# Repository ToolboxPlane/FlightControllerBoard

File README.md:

View this project on [CADLAB.io](https://cadlab.io/node/744). 

# FlightControllerBoard

A flight controller board for the mini Talon UAV based on a [STM32 Nucleo-32](http://www.st.com/content/st_com/en/products/evaluation-tools/product-evaluation-tools/mcu-eval-tools/stm32-mcu-eval-tools/stm32-mcu-nucleo/nucleo-l432kc.html).

Firmware availiable at [https://github.com/ToolboxBodensee/FlightController](https://github.com/ToolboxBodensee/FlightController).

## PCB

### Top layer

### Bottom Layer

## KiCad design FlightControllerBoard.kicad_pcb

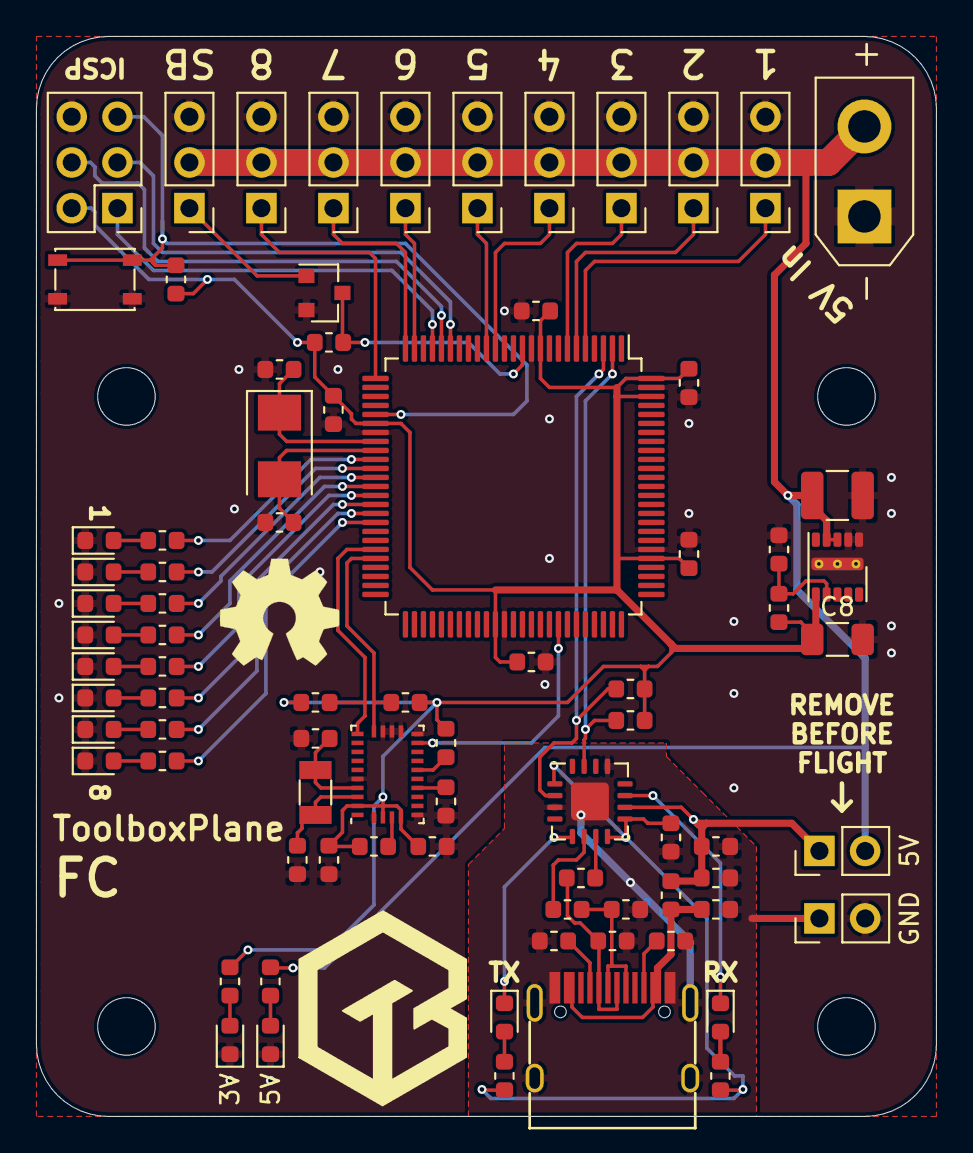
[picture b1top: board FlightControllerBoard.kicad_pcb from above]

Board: 2 copper layers, 50.0 x 60.0 mm, 85 parts (0 on the bottom side), 62 nets.

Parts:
C1, C2: 47p; C_0603_1608Metric
C3: 10nF; C_0603_1608Metric
C4, C6, C11, C12, C13, C14, C15, C16, C17, C18: 100nF; C_0603_1608Metric
C5: 4.7µF; C_0603_1608Metric
C7: 10µF; C_1210_3225Metric
C8: 22µF; C_1206_3216Metric
C9, C10: 8pF; C_0603_1608Metric
C19, C20: 9pF; C_0603_1608Metric
D1, D2: LED; LED_0603_1608Metric
D3, D4: LED_Small; LED_0603_1608Metric
D5, D6, D7, D8, D9, D10, D11, D12: LED_0603_1608Metric
FB1: 600 Ohms @ 100MHz; C_0603_1608Metric
H1, H2, H3, H4: MountingHole; MountingHole_3.2mm_M3
J1: Conn_01x02; AMASS_XT30UPB-M_1x02_P5.0mm_Vertical
J2, J3, J4, J5, J6, J7, J8, J9, J10: Conn_01x03_Male; PinHeader_1x03_P2.54mm_Vertical
J11: USB_C_Receptacle_USB2.0; USB_C_Receptacle_GT-USB-7010
J12: Conn_02x03_Odd_Even; PinHeader_2x03_P2.54mm_Vertical
JP1, JP2: Jumper_NO_Small; PinHeader_1x02_P2.54mm_Vertical
Q1: BSS138; SOT-23
R1, R2, R3: 4.7k; R_0603_1608Metric
R4: 470; R_0603_1608Metric
R5, R10, R11: 270; R_0603_1608Metric
R6, R7: 5.1k; R_0603_1608Metric
R8, R9: 27; R_0603_1608Metric
R12: 11.5k; R_0603_1608Metric
R13: 4.99k; R_0603_1608Metric
R14, R23, R24, R25, R26: 10k; R_0603_1608Metric
R15, R16, R17, R18, R19, R20, R21, R22: 100; R_0603_1608Metric
SW1: SW_Push; SW_SPST_PTS810
U1: FT230XQ; QFN-16-1EP_4x4mm_P0.65mm_EP2.1x2.1mm
U2: LMZM23600; Texas_SIL0010A_MicroSiP-10-1EP_3.8x3mm_P0.6mm_EP0.7x2.9mm_T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
U3: ATmega2560-16AU; TQFP-100_14x14mm_P0.5mm
U4: BNO055; LGA-28_5.2x3.8mm_P0.5mm
Y1: 16MHz; Crystal_SMD_5032-2Pin_5.0x3.2mm
Y2: 32.768kHz; Crystal_SMD_3215-2Pin_3.2x1.5mm

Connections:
+3V3: C8.1, C11.2, C12.2, C13.2, C14.2, C15.2, C16.1, C18.1, J12.2, R1.1, R2.1, R3.1, R5.1, R12.1, R14.1, R23.1, R24.1, R25.1, R26.2, U2.6, U3.10, U3.31, U3.61, U3.80, U3.98, U3.100, U4.3, U4.5, U4.28
+5V: C7.1, J1.2, J2.2, J3.2, J4.2, J5.2, J6.2, J7.2, J8.2, J9.2, J10.2, JP1.2, R4.1, U2.3, U2.4
/ATMega/MISO: J12.1, U3.22
/ATMega/MOSI: J12.4, U3.21
/ATMega/RX0: R1.2, U1.15, U3.2
/ATMega/RX1: R23.2, U3.45, U4.20
/ATMega/SCK: J12.3, U3.20
/ATMega/~RESET~: J12.5, R14.2, SW1.2, U3.30
/BNO/INT: U3.68, U4.14
/BNO/RX: R24.2, U3.46, U4.19
/FT230/5VOUT: C4.1, C5.1, FB1.1, JP1.1, U1.10
/FT230/RX: R2.2, U1.2, U3.3
/PWM1: J2.1, U3.24
/PWM2: J3.1, U3.25
/PWM3: J4.1, U3.26
/PWM4: J5.1, U3.5
/PWM5: J6.1, U3.6
/PWM6: J7.1, U3.7
/PWM7: J8.1, U3.15
/PWM8: J9.1, U3.16
/SBUS: J10.1, Q1.1
/~SBUS: Q1.3, R3.2, U3.12
GND: C7.2, C8.2, C9.2, C10.2, C11.1, C12.1, C13.1, C14.1, C15.1, C16.2, C17.1, C18.2, C19.2, C20.2, D1.1, D2.1, D5.1, D6.1, D7.1, D8.1, D9.1, D10.1, D11.1, D12.1, J1.1, J2.3, J3.3, J4.3, J5.3, J6.3, J7.3, J8.3, J9.3, J10.3, J12.6, JP2.2, Q1.2, R13.1, SW1.1, U2.1, U2.2, U2.11, U3.11, U3.32, U3.62, U3.81, U3.99, U4.2, U4.6, U4.15, U4.16, U4.17, U4.18, U4.25
GNDS: C1.2, C2.2, C3.2, C4.2, C5.2, C6.2, J11.A1, J11.A12, J11.B1, J11.B12, J11.S1, JP2.1, R6.1, R7.1, U1.3, U1.13, U1.17
unnamed: C1.1, J11.A7, J11.B7, R8.2
unnamed: C2.1, J11.A6, J11.B6, R9.2
unnamed: C6.1, R10.1, R11.1, U1.1, U1.8, U1.9
unnamed: C9.1, U3.34, Y1.2
unnamed: C10.1, U3.33, Y1.1
unnamed: C17.2, U4.9
unnamed: C19.1, U4.26, Y2.1
unnamed: C20.1, U4.27, Y2.2
unnamed: D1.2, R4.2
unnamed: D2.2, R5.2
unnamed: D3.1, U1.11
unnamed: D3.2, R10.2
unnamed: D4.1, U1.5
unnamed: D4.2, R11.2
unnamed: D5.2, R15.2
unnamed: D6.2, R16.2
unnamed: D7.2, R17.2
unnamed: D8.2, R18.2
unnamed: D9.2, R19.2
unnamed: D10.2, R20.2
unnamed: D11.2, R21.2
unnamed: D12.2, R22.2
unnamed: J11.A5, R6.2
unnamed: J11.B5, R7.2
unnamed: R8.1, U1.7
unnamed: R9.1, U1.6
unnamed: R12.2, R13.2, U2.7
unnamed: R15.1, U3.35
unnamed: R16.1, U3.36
unnamed: R17.1, U3.37
unnamed: R18.1, U3.38
unnamed: R19.1, U3.39
unnamed: R20.1, U3.40
unnamed: R21.1, U3.41
unnamed: R22.1, U3.42
unnamed: R25.2, U4.11
unnamed: R26.1, U4.4
VBUS: C3.1, FB1.2, J11.A4, J11.A9, J11.B4, J11.B9

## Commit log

2017-04-17 Sonar, I2C Expansion Ports, Logo, Various Improvements
2017-04-18 preview images for documentation
2017-04-18 Update README.md
    added images to readme
2017-04-18 changed version to 8.1.1
2017-04-18 fixed toolbox logo
2017-04-18 added reset header
2017-04-18 added mounting holes, removed BNO-055 mounting holes
2017-04-20 power LEDs
2017-04-20 capacitors, dimensions, reset button
2017-04-20 various improvements, mostly silkscreen labels
2017-04-21 fixed naming of D1/D0 and SBUS connection
2017-04-21 removed GPIO, I2C Ports, added expansion port
2017-04-21 smaller board footprint, added reset to port
2017-04-21 rounded edges
2017-04-22 Added SBUS, I²C and UART LEDs
2017-04-22 Removed Eagle Files
2017-04-23 Fixed several issues
2017-04-23 Added more files to gitignore
2017-05-11 jumper to select between SBUS and !SBUS
2017-05-11 eeprom and stuff
2017-05-13 various fixes
2017-10-20 updated gitignore to include gerber files
    Source: https://github.com/github/gitignore/blob/master/Eagle.gitignore
2017-10-22 eagle 8.4.0
2017-10-23 sbus inverter spice setup
2017-10-23 i2c level shifting simulation setup
2017-10-23 power led simulation setup
2017-10-23 filtering capacitor simulation setup
2017-10-23 nucleo simulation setup
2017-10-23 EEPROM simulation setup
2017-10-23 signal LED simulation setup
2018-03-09 Backlink to CADLAB.io has been added.
2018-10-20 Started FC4
2018-10-20 First draft of the schematic finished
2018-10-20 Initial draft for the layout
2018-10-21 Small changes, added reset button
2018-10-30 Improved the design
2018-11-05 Spannungsregler
2018-11-05 FTDI hauptsächlich
2018-11-05 LED alignment
2018-12-02 cleanup
    airwire in pad/alignment
2018-12-02 led placement on grid
2018-12-02 connected LEDs
2018-12-02 led labels
2018-12-02 aligned atmega breakout vias
2018-12-02 atmega breakout cleanup
2018-12-02 isp, reset button, gnd polygon
2018-12-02 reset, alignment, caps
    reset button
    aligned sbus inverter to grid
    moved decoupling cap to sensible position
2018-12-02 minor changes to usb layout
2018-12-02 changed caps to sparkfun lib
2018-12-02 changed LEDs to sparkfun lib
2018-12-02 changed resistors to sparkfun lib
    how nice, all the 0603 parts are the same size now.
2018-12-02 move led resistors up
2018-12-02 fixed obviously wrong DRC errors
    (?)
2019-04-03 And Now for Something Completely Different
2019-04-03 LMZM23600 from official kicad lib
2019-04-03 add gitignore
2019-04-03 remove temporary file
    (added by accident)
2019-04-03 add fp-info-cache to gitignore
2019-04-03 update PCB to match schematic changes
2019-04-04 use submodule for FT230
2019-04-04 pullups, jumpers
2019-04-05 LED, Mounting Holes
    LEDs to register L
    Mounting Holes
    XT30
2019-04-06 layout
2019-04-06 fix Y1 connection
2019-04-06 small layout fixes
2019-04-07 silkscreen logos
2019-04-07 rebuild zones
2019-04-07 fix power input
2019-04-07 optimize gnd connections
2019-04-07 added NCs to satisfy ERC
2019-04-27 fix LED resistor values
